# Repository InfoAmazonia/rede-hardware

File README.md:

# Mãe d'Água - Hardware

An open hardware to monitor water quality in real time. The system will help infer physicochemical properties and variables that differentiate drinkable from contaminated water. Mãe d'Água is part of the project <a href="http://infoamazonia.org/projects/infoamazonia-network/">InfoAmazonia Network</a>.

The device will measure acidity in water by potential of hydrogen (pH), oxidation - reduction potential (ORP), conductivity, temperature and barometric pressure in the water level, which are important factors to consider when assessing water quality for human consumption.

The hardware is modular:
- Module 1 (M1): composed by Arduino Mega, it is responsible for all processing of information captured by the sensors and the entire power supply (connected to an external source).
- Module 2 (M2): Arduino shield (in this repository), designed using Eagle platform, with the barometric pressure sensor and connectors for coupling the pH, ORP, conductivity and water temperature sensors. This way, it is possible to select modules that are appropriate aiming the best cost-benefit ratio of specific desired application.
- Module 3 (M3): responsible for mobile communication (2G), capable of transmitting data by Internet and by SMS to the InfoAmazonia Network internet server. As auxiliary data access strategy, the M2 also features a SD memory card slot.

The complete hardware will capture a reading of each of the sensors per hour, and send them to our remote server, which will provide visualization in an open database.

The development files of the project's hardware/software can be found at:
- Hardware's design: https://github.com/InfoAmazonia/rede-hardware
- Firmware: https://github.com/InfoAmazonia/rede-firmware
- Website for data visualization: https://github.com/InfoAmazonia/rede-site
- SMS backend (to receive data from the equipments and to send alerts to the communities): https://github.com/InfoAmazonia/rede-sms

This hardware is licensed under the <a href="http://www.ohwr.org/attachments/2388/cern_ohl_v_1_2.txt">CERN Open Hardware License Version 1.2.</a>

The EC sensor of this project is based on <a href="http://publiclab.org/notes/donblair/09-30-2014/coqui-bbv1-0">Coqui BBv1.0.</a>

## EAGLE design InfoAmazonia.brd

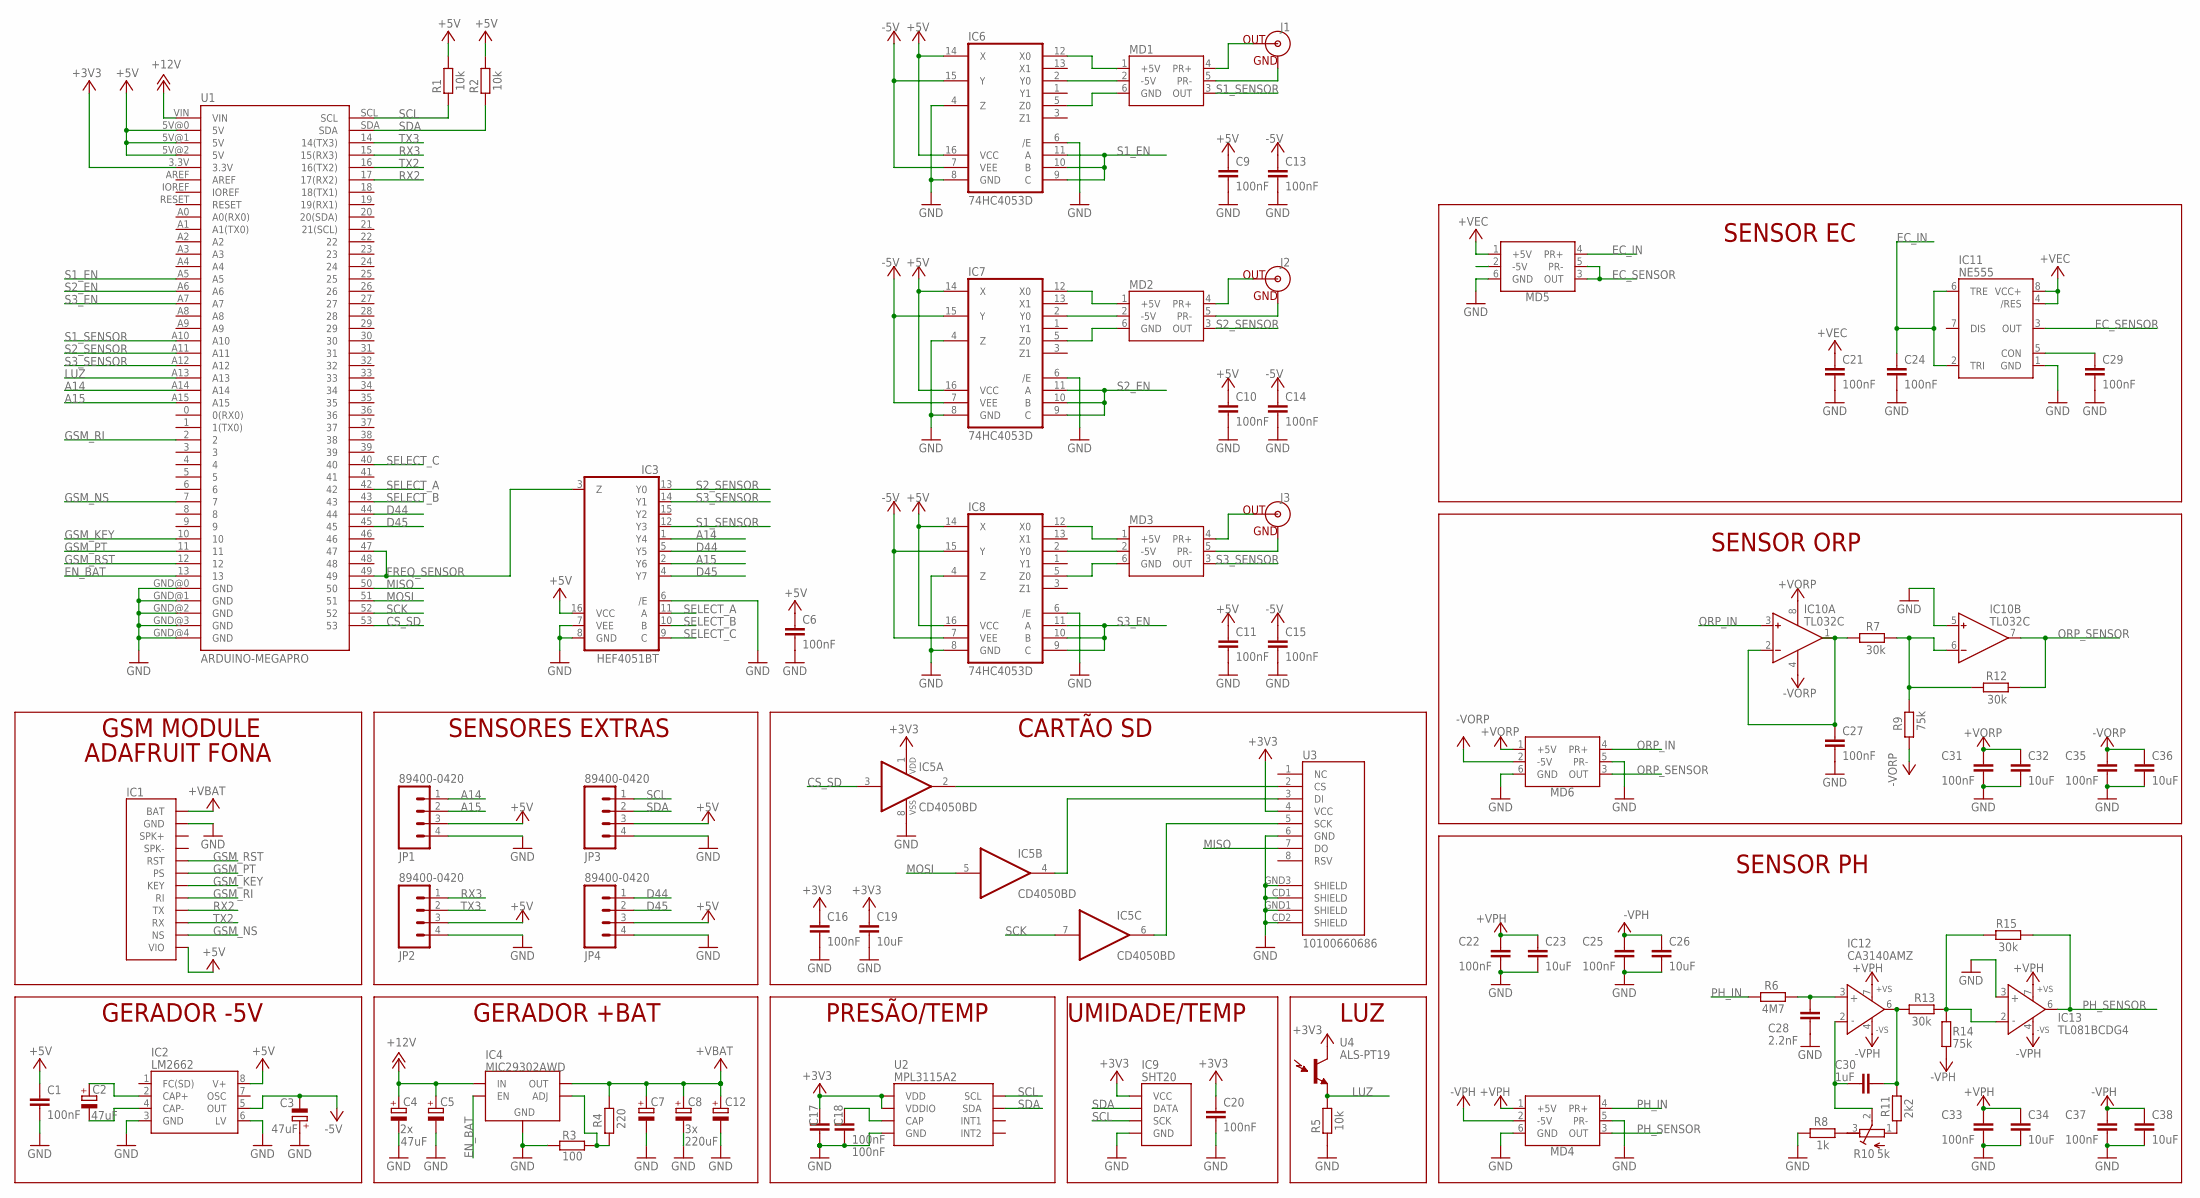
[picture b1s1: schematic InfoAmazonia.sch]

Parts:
C1, C6, C9, C10, C11, C13, C14, C15, C16, C17, C18, C20, C21, C22, C24, C25, C27, C29, C31, C33, C35, C37: 100nF; C0603
C2, C3: 47uF; SMC_B
C4, C5: 47uF; UD-6,3X5,8_NICHICON
C7, C8, C12: 220uF; UD-6,3X5,8_NICHICON
C19, C23, C26, C32, C34, C36, C38: 10uF; C0603
C28: 2.2nF; C0603
C30: 1uF; C0603
IC1: ADAFRUIT FONA; ADAFRUIT_FONA
IC2: LM2662; SO8
IC3: HEF4051BT; SO16
IC4: MIC29302AWD; TO252-5
IC5: CD4050BD; SO16
IC6, IC7, IC8: 74HC4053D; SO16
IC9: SHT20; SHT2X
IC10: TL032C; SO8
IC11: NE555; SO8
IC12: CA3140AMZ; SO8
IC13: TL081BCDG4; SO8
J1, J2, J3: 31-5431-10RFX; BNC
JP1, JP2, JP3, JP4: 89400-0420; JST-4-PTH-VERT
MD1, MD2, MD3, MD4, MD5, MD6: INFO-AMAZONIA-MODULE
R1, R2, R5: 10k; R0603
R3: 100; R0603
R4: 220; R0603
R6: 4M7; R0603
R7, R12, R13, R15: 30k; R0603
R8: 1k; R0603
R9, R14: 75k; R0603
R10: 5k; RTRIM3296W
R11: 2k2; R0603
U1: ARDUINO-MEGAPRO; ARDUINO_MEGA_2560
U2: MPL3115A2; LGA8
U3: 10100660686; MICRO-SD-SOCKET-PP
U4: ALS-PT19

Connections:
+3V3: C16.1, C17.1, C19.1, C20.1, IC5.1 (VDD), IC9.5 (VCC), U1.3.3V, U2.1 (VDD), U2.4 (VDDIO), U3.4 (VCC), U4.C (C1)
+5V: C1.1, C6.1, C9.1, C10.1, C11.1, IC1.12 (VIO), IC2.8 (V+), IC3.16 (VCC), IC6.14 (X), IC6.16 (VCC), IC7.14 (X), IC7.16 (VCC), IC8.14 (X), IC8.16 (VCC), JP1.3, JP2.3, JP3.3, JP4.3, R1.2, R2.2, U1.5V@0 (5V), U1.5V@1 (5V), U1.5V@2 (5V)
+12V: C4.+, C5.+, IC4.2 (IN), U1.VIN
+VBAT: C7.+, C8.+, C12.+, IC1.1 (BAT), IC4.4 (OUT), R4.1
+VEC: C21.1, IC11.4 (/RES), IC11.8 (VCC+), MD5.1 (+5V)
+VORP: C31.1, C32.1, IC10.8 (V+), MD6.1 (+5V)
+VPH: C22.1, C23.1, C33.1, C34.1, IC12.7 (+VS), IC13.7 (+VS), MD4.1 (+5V)
-5V: C3.-, C13.1, C14.1, C15.1, IC2.5 (OUT), IC6.7 (VEE), IC6.15 (Y), IC7.7 (VEE), IC7.15 (Y), IC8.7 (VEE), IC8.15 (Y)
-VORP: C35.1, C36.1, IC10.4 (V-), MD6.2 (-5V), R9.2
-VPH: C25.1, C26.1, C37.1, C38.1, IC12.4 (-VS), IC13.4 (-VS), MD4.2 (-5V), R14.2
A14: IC3.1 (Y4), JP1.1, U1.A14
A15: IC3.2 (Y6), JP1.2, U1.A15
CS_SD: IC5.3 (I), U1.53
D44: IC3.5 (Y5), JP4.1, U1.44
D45: IC3.4 (Y7), JP4.2, U1.45
EC_IN: C24.1, IC11.2 (TRI), IC11.6 (TRE), MD5.4 (PR+)
EC_SENSOR: IC11.3 (OUT), MD5.3 (OUT), MD5.5 (PR-)
EN_BAT: IC4.1 (EN), U1.13
FC(SD): IC2.1 (FC(SD))
FREQ_SENSOR: IC3.3 (Z), U1.47, U1.49
GND: C1.2, C3.+, C4.-, C5.-, C6.2, C7.-, C8.-, C9.2, C10.2, C11.2, C12.-, C13.2, C14.2, C15.2, C16.2, C17.2, C18.2, C19.2, C20.2, C21.2, C22.2, C23.2, C24.2, C25.2, C26.2, C27.2, C28.2, C29.2, C31.2, C32.2, C33.2, C34.2, C35.2, C36.2, C37.2, C38.2, IC1.2 (GND), IC1.K1 (GND), IC1.K2 (GND), IC2.3 (GND), IC2.6 (LV), IC3.6 (/E), IC3.7 (VEE), IC3.8 (GND), IC4.3 (GND), IC4.6 (GND), IC5.8 (VSS), IC6.4 (Z), IC6.6 (/E), IC6.8 (GND), IC7.4 (Z), IC7.6 (/E), IC7.8 (GND), IC8.4 (Z), IC8.6 (/E), IC8.8 (GND), IC9.2 (GND), IC9.7 (GND), IC10.5 (IN+), IC11.1 (GND), IC13.3 (IN+), JP1.4, JP2.4, JP3.4, JP4.4, MD4.5 (PR-), MD4.6 (GND), MD5.6 (GND), MD6.5 (PR-), MD6.6 (GND), R3.1, R5.1, R8.2, U1.GND@0 (GND), U1.GND@1 (GND), U1.GND@2 (GND), U1.GND@3 (GND), U1.GND@4 (GND), U2.3 (GND), U3.6 (GND), U3.CD1 (SHIELD), U3.CD2 (SHIELD), U3.GND1 (SHIELD), U3.GND3 (SHIELD)
GSM_KEY: IC1.7 (KEY), U1.10
GSM_NS: IC1.11 (NS), U1.7
GSM_PT: IC1.6 (PS), U1.11
GSM_RI: IC1.8 (RI), U1.2
GSM_RST: IC1.5 (RST), U1.12
LUZ: R5.2, U1.A13, U4.E (E1)
MISO: U1.50, U3.7 (DO)
MOSI: IC5.5 (I), U1.51
unnamed: J1.GND, MD1.5 (PR-)
unnamed: C28.1, IC12.3 (IN+), R6.2
unnamed: C30.1, IC12.2 (IN-), R10.2 (S)
unnamed: C30.2, IC12.6 (OUT), R11.2, R13.2
unnamed: IC13.2 (IN-), R13.1, R14.1, R15.1
unnamed: R8.1, R10.3 (E)
unnamed: C18.1, U2.2 (CAP)
unnamed: R10.1 (A), R11.1
unnamed: J1.S (OUT), MD1.4 (PR+)
unnamed: C29.1, IC11.5 (CON)
unnamed: J2.GND, MD2.5 (PR-)
unnamed: J2.S (OUT), MD2.4 (PR+)
unnamed: J3.GND, MD3.5 (PR-)
unnamed: C2.-, IC2.4 (CAP-)
unnamed: C27.1, IC10.1 (OUT), IC10.2 (IN-), R7.2
unnamed: C2.+, IC2.2 (CAP+)
unnamed: IC10.6 (IN-), R7.1, R9.1, R12.1
unnamed: IC4.5 (ADJ), R3.2, R4.2
unnamed: IC5.6 (O), U3.5 (SCK)
unnamed: IC5.4 (O), U3.3 (DI)
unnamed: IC5.2 (O), U3.2 (CS)
unnamed: J3.S (OUT), MD3.4 (PR+)
unnamed: IC6.12 (X0), MD1.1 (+5V)
unnamed: IC6.2 (Y0), MD1.2 (-5V)
unnamed: IC6.5 (Z0), MD1.6 (GND)
unnamed: IC7.5 (Z0), MD2.6 (GND)
unnamed: IC7.2 (Y0), MD2.2 (-5V)
unnamed: IC7.12 (X0), MD2.1 (+5V)
unnamed: IC8.12 (X0), MD3.1 (+5V)
unnamed: IC8.2 (Y0), MD3.2 (-5V)
unnamed: IC8.5 (Z0), MD3.6 (GND)
ORP_IN: IC10.3 (IN+), MD6.4 (PR+)
ORP_SENSOR: IC10.7 (OUT), MD6.3 (OUT), R12.2
PH_IN: MD4.4 (PR+), R6.1
PH_SENSOR: IC13.6 (OUT), MD4.3 (OUT), R15.2
RX2: IC1.9 (TX), U1.17 (17(RX2))
RX3: JP2.1, U1.15 (15(RX3))
S1_EN: IC6.9 (C), IC6.10 (B), IC6.11 (A), U1.A5
S1_SENSOR: IC3.12 (Y3), MD1.3 (OUT), U1.A10
S2_EN: IC7.9 (C), IC7.10 (B), IC7.11 (A), U1.A6
S2_SENSOR: IC3.13 (Y0), MD2.3 (OUT), U1.A11
S3_EN: IC8.9 (C), IC8.10 (B), IC8.11 (A), U1.A7
S3_SENSOR: IC3.14 (Y1), MD3.3 (OUT), U1.A12
SCK: IC5.7 (I), U1.52
SCL: IC9.6 (SCK), JP3.1, R1.1, U1.SCL, U2.8 (SCL)
SDA: IC9.1 (DATA), JP3.2, R2.1, U1.SDA, U2.7 (SDA)
SELECT_A: IC3.11 (A), U1.42
SELECT_B: IC3.10 (B), U1.43
SELECT_C: IC3.9 (C), U1.40
TX2: IC1.10 (RX), U1.16 (16(TX2))
TX3: JP2.2, U1.14 (14(TX3))

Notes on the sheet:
SENSOR ORP
SENSOR PH
PRESÃO/TEMP
UMIDADE/TEMP
GERADOR -5V
GERADOR +BAT
LUZ
CARTÃO SD
SENSOR EC
GSM MODULE
ADAFRUIT FONA
SENSORES EXTRAS

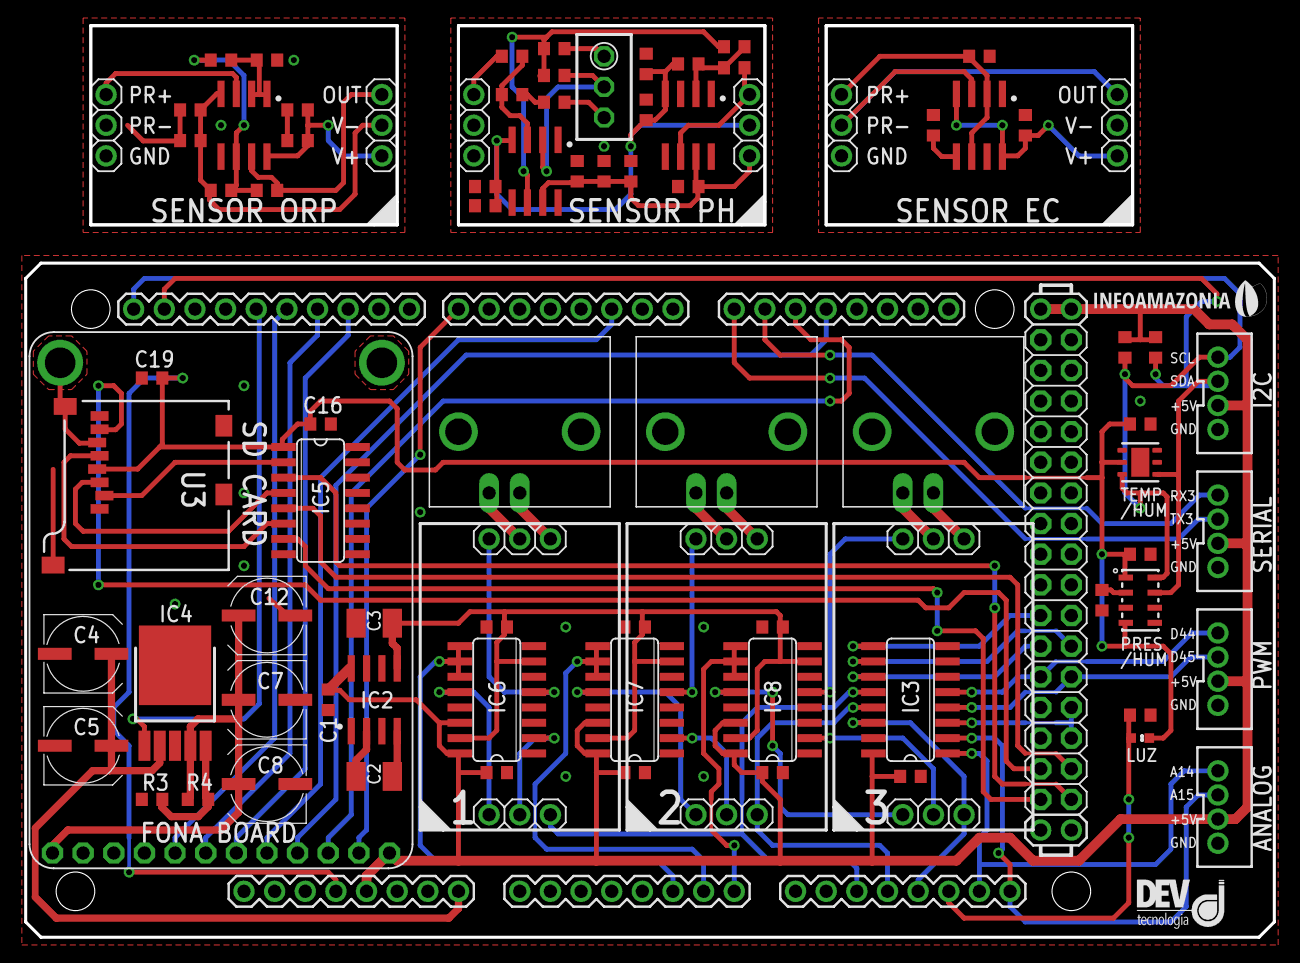
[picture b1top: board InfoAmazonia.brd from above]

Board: 2 copper layers, 103.5 x 75.6 mm, 85 parts (0 on the bottom side), 79 nets.

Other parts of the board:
U$1: LOGO-INFO-0.38
U$2: LOGO-DEV-0.9

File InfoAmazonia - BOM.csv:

"Qty";"Value";"Device";"Package";"Parts";"Description";"MF";"MPN";"OC_FARNELL";"OC_NEWARK";"PROD_ID";
"1";"100";"R-EU_R0603";"R0603";"R3";"RESISTOR, European symbol";"";"";"";"";"";
"22";"100nF";"C-EUC0603";"C0603";"C1, C6, C9, C10, C11, C13, C14, C15, C16, C17, C18, C20, C21, C22, C24, C25, C27, C29, C31, C33, C35, C37";"CAPACITOR, European symbol";"";"";"";"";"";
"1";"10100660686";"USD-SOCKETNEW";"MICRO-SD-SOCKET-PP";"U3";"microSD Socket";"";"";"";"";"";
"3";"10k";"R-EU_R0603";"R0603";"R1, R2, R5";"RESISTOR, European symbol";"";"";"";"";"";
"7";"10uF";"C-EUC0603";"C0603";"C19, C23, C26, C32, C34, C36, C38";"CAPACITOR, European symbol";"";"";"";"";"";
"1";"1k";"R-EU_R0603";"R0603";"R8";"RESISTOR, European symbol";"";"";"";"";"";
"1";"1uF";"C-EUC0603";"C0603";"C30";"CAPACITOR, European symbol";"";"";"";"";"";
"1";"2.2nF";"C-EUC0603";"C0603";"C28";"CAPACITOR, European symbol";"";"";"";"";"";
"1";"220";"R-EU_R0603";"R0603";"R4";"RESISTOR, European symbol";"";"";"";"";"";
"3";"220uF";"CPOL-EUUD6,3-5,8";"UD-6,3X5,8_NICHICON";"C7, C8, C12";"POLARIZED CAPACITOR, European symbol";"";"";"";"";"";
"1";"2k2";"R-EU_R0603";"R0603";"R11";"RESISTOR, European symbol";"";"";"";"";"";
"4";"30k";"R-EU_R0603";"R0603";"R7, R12, R13, R15";"RESISTOR, European symbol";"";"";"";"";"";
"3";"31-5431-10RFX";"BNCPTH";"BNC";"J1, J2, J3";"BNC Connector, Mouser Part# 5227161";"";"";"";"";"";
"2";"47uF";"CPOL-EUSMC_B";"SMC_B";"C2, C3";"POLARIZED CAPACITOR, European symbol";"";"";"";"";"";
"2";"47uF";"CPOL-EUUD6,3-5,8";"UD-6,3X5,8_NICHICON";"C4, C5";"POLARIZED CAPACITOR, European symbol";"";"";"";"";"";
"1";"4M7";"R-EU_R0603";"R0603";"R6";"RESISTOR, European symbol";"";"";"";"";"";
"1";"5k";"RTRIM329W";"RTRIM3296W";"R10";"Trimm resistor";"";"";"";"";"";
"3";"74HC4053D";"4053D";"SO16";"IC6, IC7, IC8";"Triple 2-channel ANALOG MULTIPLEXER";"";"";"";"";"";
"2";"75k";"R-EU_R0603";"R0603";"R9, R14";"RESISTOR, European symbol";"";"";"";"";"";
"4";"89400-0420";"M04JST-PTH-VERT";"JST-4-PTH-VERT";"JP1, JP2, JP3, JP4";"Header 4";"";"";"";"";"";
"1";"ADAFRUIT FONA";"ADAFRUIT_FONA";"ADAFRUIT_FONA";"IC1";"";"";"";"";"";"";
"1";"ALS-PT19";"LIGHTSENSORALS";"ALS-PT19";"U4";"Ambient Light Sensor";"";"";"";"";"IC-11836";
"1";"ARDUINO-MEGAPRO";"ARDUINO-MEGAPRO";"ARDUINO_MEGA_2560";"U1";"Arduino Mega board footprint";"";"";"";"";"";
"1";"CA3140AM Z";"AMPOP";"SO8";"IC12";"High Performance Video Op Amp";"ALTERA CORPORATION";"AD811JRZ";"9426485";"82H2980";"";
"1";"CD4050BD";"4050D";"SO16";"IC5";"Hex non-inverting BUFFER";"";"";"";"";"";
"1";"HEF4051BT";"4051D";"SO16";"IC3";"8-channel ANALOG MULTIPLEXER";"";"";"";"";"";
"6";"INFO-AMAZONIA-MODULE";"INFO-AMAZONIA-MODULE";"INFO-AMAZONIA-MODULE";"MD1, MD2, MD3, MD4, MD5, MD6";"";"";"";"";"";"";
"1";"LM2662";"LM2662";"SO8";"IC2";"";"";"";"";"";"";
"1";"MIC29302AWD";"MIC29XXX";"TO252-5";"IC4";"";"";"";"";"";"";
"1";"MPL3115A2";"MPL3115A2LGA8";"LGA8";"U2";"Altimeter/Pressure Sensor, I2C, 1.95V-3.6V supply, 50 to 110kPa";"";"";"";"";"IC-10869";
"1";"NE555";"NE555";"SO8";"IC11";"General purpose bipolar Timer";"";"";"";"";"";
"1";"SHT20";"SHT2X";"SHT2X";"IC9";"";"";"";"";"";"";
"1";"TL032C";"AMPOP_2R";"SO8";"IC10";"Dual Precision, Low Cost, High Speed BiFET Op Amp";"ALTERA CORPORATION";"AD712KRZ";"1263975";"59K4556";"";
"1";"TL081BCDG4";"AMPOP";"SO8";"IC13";"High Performance Video Op Amp";"ALTERA CORPORATION";"AD811JRZ";"9426485";"82H2980";"";

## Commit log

2015-04-02 - pHmetro feito
2015-04-08 - Placa criada
2015-04-14 -Acho que não adicionou praticamente nada
2015-04-16 [INFOA-19]
    - Alguns valores de componentes alterados, bom mandado pra avaliação
2015-04-22 - SD adicionado
2015-04-27 - Decidido que sera utilizado o sensor do rifle pra EC
2015-04-28 - Adicionado sensor de EC
2015-04-28 - Terminado o esquematico
2015-04-28 - Acho que mudei uns detlhes cosmeticos
2015-05-08 [INFOA-26]
    - Mudanças de conector JST PH
2015-05-14 [INFOA-26]
    - Placa roteada pelo Anderson
2015-05-29 - Mudanças cosmeticas na parte dos sensores
2015-05-29 - Mudancas no silkscreen da placa
2015-06-04 - Ajustes depois do prototipo
2015-06-08 - Alteracao nos modulos externos. Agora devem caber em uma protoboard.
2015-06-09 - Mudanças bem minimas (Valores de capacitor por exemplo)
2015-06-10 - Agora os modulos tem tamanho definido via componente nas bibliotecas
2015-06-11 - Mudanca no pino rx/tx do fona
2015-06-17 - Commit antes de tentar transferir os sensores de temp/luz/presao para a lateral direita
2015-06-23 - Coloquei os sensores pro lado
2015-06-27 - Roteado os sensores do lado
2015-07-15 - Mudanca de posicao de alguns componentes basicos
2015-07-17 - Adicionado o controlador de tensões, falta rotear
2015-07-18 - Faltando somente distribuicao do +3V3 e decidir se a interrupcao do sensor de pressao fica
2015-07-20 - Roteamento terminado, pendendo revisão
2015-07-20 - Adicionado tented vias
2015-07-20 - Versao enviada para cotacao
2015-07-20 - Mudancas cosmeticas
2015-07-20 - Versao enviada para producao
2015-07-20 - Versao enviada para fabricacao
2015-07-21 - Mudado o codigo de alguns componentes para bater com o BOM
2015-08-04 - Adicionado o assembly drawing
2015-08-06 - Adicionado a licenca cern_ohl_v_1_2.txt
2015-08-26 - Adicionado o logo da infoamazonia nas placas
2015-08-26 - Adicionado .pdf com o esquematico
